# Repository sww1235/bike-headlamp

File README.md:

# bike-headlamp
Code and ECAD work for a helmet mounted bikelight

part of my edc-carry project

700mA * 12V = 8.4W -> 10W

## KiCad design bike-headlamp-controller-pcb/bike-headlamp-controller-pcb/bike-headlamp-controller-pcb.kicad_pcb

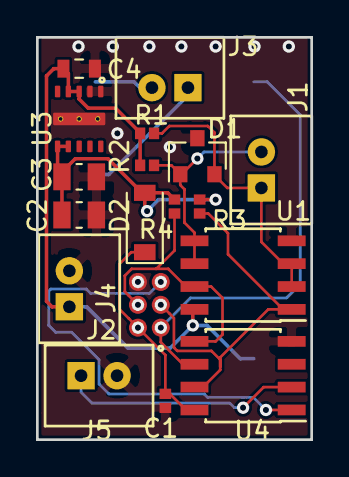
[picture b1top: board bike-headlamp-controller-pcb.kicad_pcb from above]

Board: 2 copper layers, 15.2 x 22.4 mm, 19 parts (1 on the bottom side), 13 nets.

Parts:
C1: 0.1uF; C_0402_1005Metric
C2, C3: 22uF; C_0805_2012Metric
C4: 10uF; C_0603_1608Metric
D1: BAT54A; SOT-23
D2: MBR0520LT; D_SOD-123
J1: i2c_hv; JST-2pole
J2: 12V in; JST-2pole
J3: LED; JST-2pole
J4: ISC Header; isc-pogo-pins
J5: switch; JST-2pole
R1, R2: 750Ω; R_0402_1005Metric
R3, R4: 10kΩ; R_0402_1005Metric
U1: P82B96; SOIC-8_3.9x4.9mm_P1.27mm
U2: MiniPuck; Minipuck-smd
U3: LMZM23600V5SILT; SIL0010A
U4: ATTINY85-20SU; SOIC-8_3.9x4.9mm_P1.27mm

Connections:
+5V: C2.1, C3.1, D2.2, R3.2, R4.2, U3.6, U3.7
+12V: C4.1, J2.1, R1.2, R2.2, U1.8, U2.1, U3.3, U3.4
/+5V_MCU: C1.1, D2.1, J4.2, U4.8
/LED+: J3.1, U2.4
/LED-: J3.2, U2.5
/LED_PWM: J4.1, U2.3, U4.6
/MOSI: J4.4, R4.1, U1.7, U4.5
/SCK: J4.3, R3.1, U1.1, U4.7
/SCL_hv: D1.2, J1.1, R1.1, U1.2, U1.3
/SDA_hv: D1.1, J1.2, R2.1, U1.5, U1.6
/SW-IN: J5.1, U4.2
/~RESET: J4.5, U4.1
GND: C1.2, C2.2, C3.2, C4.2, D1.3, J2.2, J4.6, J5.2, U1.4, U2.2, U3.1, U3.2, U3.11, U4.4

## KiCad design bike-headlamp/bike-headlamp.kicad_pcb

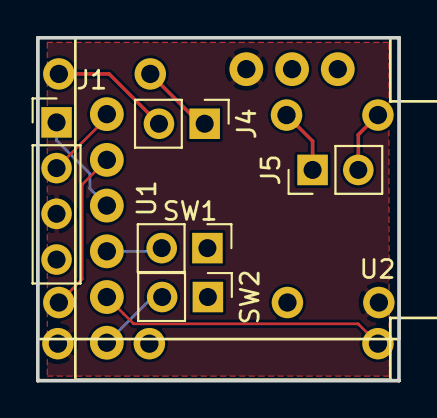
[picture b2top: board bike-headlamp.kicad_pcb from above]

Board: 2 copper layers, 20.1 x 19.1 mm, 8 parts (1 on the bottom side), 12 nets.

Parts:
J1: HARNESS5-8; Pin_Header_Straight_1x04_Pitch2.54mm
J4: LED1; Pin_Header_Straight_1x02_Pitch2.54mm
J5: LED2; Pin_Header_Straight_1x02_Pitch2.54mm
SW1: FRONT; Pin_Header_Straight_1x02_Pitch2.54mm
SW2: BACK; Pin_Header_Straight_1x02_Pitch2.54mm
U1: Digispark
U2, U3: MiniPuck; MiniPuck-Pinned

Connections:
+12V: J1.3, U1.7, U2.1, U3.1
/LED1+: J4.1, U2.4
/LED1-: J4.2, U2.5
/LED1-PWM: U1.2, U2.3
/LED2+: J5.1, U3.4
/LED2-: J5.2, U3.5
/LED2-PWM: U1.5, U3.3
/SCL: J1.1, U1.3
/SDA: J1.2, U1.1
/SW-BACK: SW2.2, U1.6
/SW-FRONT: SW1.2, U1.4
GNDREF: J1.4, SW1.1, SW2.1, U1.8, U2.2, U3.2

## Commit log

2016-12-11 adding kicad gitignore
2016-12-11 added gitignore for model
2016-12-11 removing .plt file
2016-12-11 added strobe switch
2016-12-11 updated schematic plot
2017-09-21 Modified schematic for use with minipuck and new design
2017-09-21 starting pcb layout
2017-09-21 finalized board?
2017-09-26 Started code
2017-09-27 Renaming main ino file
2017-09-27 fixing renaming error
2017-09-27 Started button debouncing code
2017-09-27 Started working on debouncing switches
2017-09-28 removing vectorworks model
2017-09-28 Add overall gitignore
2017-09-28 Update overall gitignore
2017-09-28 Adding stp and wrl files
2017-09-28 Create LICENSE
2017-10-26 Added some comments and fixed led dimming logic
2017-10-26 Added some comments and more logic to loop
2017-10-26 Added value saving at end of loop
2018-04-05 Added power consumption calculations
2018-10-04 removing old pcb design from new branch
2018-10-04 starting new pcb design for half-housing implementation
2018-10-15 finished initial draft of pcb
2019-03-19 added tex gitignore
2019-03-19 added math tex file
2019-03-19 added explanation
